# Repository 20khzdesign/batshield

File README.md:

Batshield
=========

An audio shield for arduino intended to develop audio synthesis and filtering.

Features
========

- MIDI input
- MIDI output
- Mic/Line input
- Line output
- 2 PWM output
- 4 switches
- 4 push buttons
- 5 knobs

The line output have been designed in order to be compatible with mozzi library
(http://sensorium.github.io/Mozzi/)

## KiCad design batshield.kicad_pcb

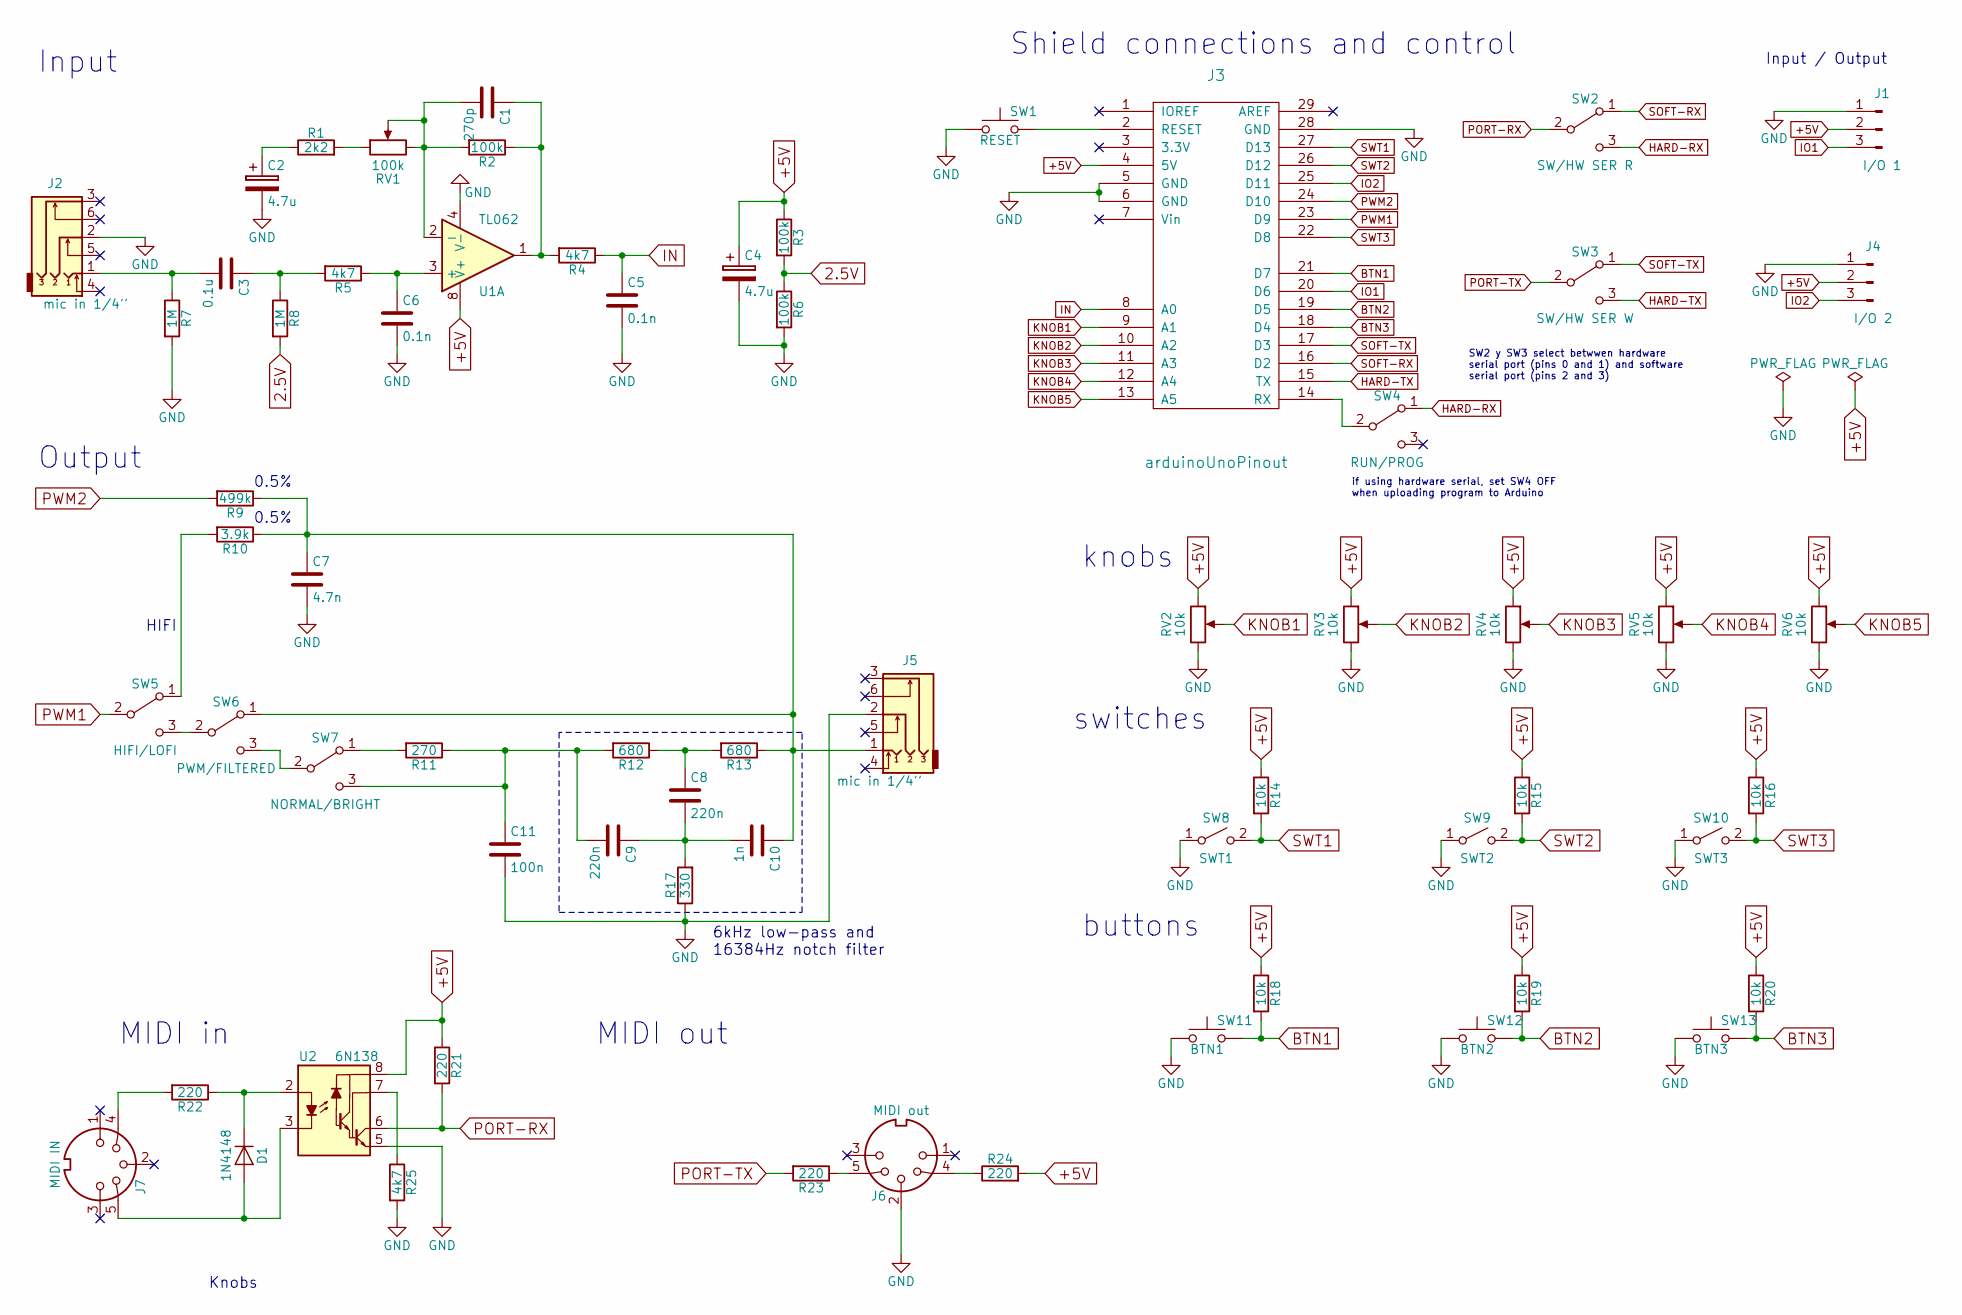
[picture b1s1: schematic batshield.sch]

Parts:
C1: 270p; C_Disc_D5.0mm_W2.5mm_P5.00mm
C2, C4: 4.7u; CP_Radial_D5.0mm_P2.50mm
C3: 0.1u; C_Disc_D5.0mm_W2.5mm_P5.00mm
C5, C6: 0.1n; C_Disc_D5.0mm_W2.5mm_P5.00mm
C7: 4.7n; C_Disc_D5.0mm_W2.5mm_P5.00mm
C8, C9: 220n; C_Disc_D5.0mm_W2.5mm_P5.00mm
C10: 1n; C_Disc_D5.0mm_W2.5mm_P5.00mm
C11: 100n; C_Disc_D5.0mm_W2.5mm_P5.00mm
D1: 1N4148; D_DO-35_SOD27_P7.62mm_Horizontal
J1: I/O 1; Pin_Header_Straight_1x03_Pitch2.54mm
J2, J5: mic in 1/4''; Jack_Female_6,35mm_HD
J3: arduinoUnoPinout
J4: I/O 2; Pin_Header_Straight_1x03_Pitch2.54mm
J6: MIDI out; MIDI_female_5_pins
J7: MIDI IN; MIDI_female_5_pins
R1: 2k2; R_Axial_DIN0207_L6.3mm_D2.5mm_P7.62mm_Horizontal
R2, R3, R6: 100k; R_Axial_DIN0207_L6.3mm_D2.5mm_P7.62mm_Horizontal
R4, R5, R25: 4k7; R_Axial_DIN0207_L6.3mm_D2.5mm_P7.62mm_Horizontal
R7, R8: 1M; R_Axial_DIN0207_L6.3mm_D2.5mm_P7.62mm_Horizontal
R9: 499k; R_Axial_DIN0207_L6.3mm_D2.5mm_P7.62mm_Horizontal
R10: 3.9k; R_Axial_DIN0207_L6.3mm_D2.5mm_P7.62mm_Horizontal
R11: 270; R_Axial_DIN0207_L6.3mm_D2.5mm_P7.62mm_Horizontal
R12, R13: 680; R_Axial_DIN0207_L6.3mm_D2.5mm_P7.62mm_Horizontal
R14, R15, R16, R18, R19, R20: 10k; R_Axial_DIN0207_L6.3mm_D2.5mm_P7.62mm_Horizontal
R17: 330; R_Axial_DIN0207_L6.3mm_D2.5mm_P7.62mm_Horizontal
R21, R22, R23, R24: 220; R_Axial_DIN0207_L6.3mm_D2.5mm_P7.62mm_Horizontal
RV1: 100k; potenciometro_PTV09
RV2, RV3, RV4, RV5, RV6: 10k; potenciometro_PTV09
SW1: RESET; SW_PUSH_6mm_h5mm
SW2: SW/HW SER R; interruptor_spdt
SW3: SW/HW SER W; interruptor_spdt
SW4: RUN/PROG; interruptor_spdt
SW5: HIFI/LOFI; interruptor_spdt
SW6: PWM/FILTERED; interruptor_spdt
SW7: NORMAL/BRIGHT; interruptor_spdt
SW8: SWT1; interruptor_spdt
SW9: SWT2; interruptor_spdt
SW10: SWT3; interruptor_spdt
SW11: BTN1; button_spst
SW12: BTN2; button_spst
SW13: BTN3; button_spst
U1: TL062; DIP-8_W7.62mm
U2: 6N138; DIP-8_W7.62mm

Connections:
2.5V: R3.2, R6.1, R8.2
+5V: C4.1, J1.2, J3.4 (5V), J4.2, R3.1, R14.1, R15.1, R16.1, R18.1, R19.1, R20.1, R21.1, R24.2, RV2.1, RV3.1, RV4.1, RV5.1, RV6.1, U1.8 (V+), U2.8
BTN1: J3.21 (D7), R18.2, SW11.2
BTN2: J3.19 (D5), R19.2, SW12.2
BTN3: J3.18 (D4), R20.2, SW13.2
GND: C2.2, C4.2, C5.2, C6.2, C7.2, C11.2, J1.1, J2.2, J3.5 (GND), J3.6 (GND), J3.28 (GND), J4.1, J5.2, J6.2, R6.2, R7.2, R17.1, R25.2, RV2.3, RV3.3, RV4.3, RV5.3, RV6.3, SW1.1, SW8.1 (A), SW9.1 (A), SW10.1 (A), SW11.1, SW12.1, SW13.1, U1.4 (V-), U2.5; also elsewhere on the board
HARD-RX: SW2.3 (C), SW4.1 (A)
HARD-TX: J3.15 (TX), SW3.3 (C)
IN: C5.1, J3.8 (A0), R4.1
IO1: J1.3, J3.20 (D6)
IO2: J3.25 (D11), J4.3
KNOB1: J3.9 (A1), RV2.2
KNOB2: J3.10 (A2), RV3.2
KNOB3: J3.11 (A3), RV4.2
KNOB4: J3.12 (A4), RV5.2
KNOB5: J3.13 (A5), RV6.2
unnamed: C1.1, R2.1, R4.2, U1.1
unnamed: C1.2, R2.2, RV1.2, RV1.3, U1.2 (-)
unnamed: C2.1, R1.1
unnamed: C3.1, R5.2, R8.1
unnamed 20: C3.2, J2.1, R7.1; also elsewhere on the board
unnamed: C6.1, R5.1, U1.3 (+)
unnamed: C8.1, R12.1, R13.2
unnamed 23: C7.1, C10.1, J5.1, R9.1, R10.1, R13.1, SW6.1 (A); also elsewhere on the board
unnamed: C8.2, C9.1, C10.2, R17.2
unnamed: C9.2, C11.1, R11.1, R12.2, SW7.3 (C)
unnamed: D1.1 (K), R22.1, U2.2
unnamed 27: D1.2 (A), J7.5, U2.3; also elsewhere on the board
unnamed: J3.2 (RESET), SW1.2
unnamed: J3.14 (RX), SW4.2 (B)
unnamed 44: J6.4, R24.1; also elsewhere on the board
unnamed 45: J6.5, R23.1; also elsewhere on the board
unnamed 49: J7.4, R22.2; also elsewhere on the board
unnamed: R1.2, RV1.1
unnamed: R10.2, SW5.1 (A)
unnamed: R11.2, SW7.1 (A)
unnamed: R25.1, U2.7
unnamed: SW5.3 (C), SW6.2 (B)
unnamed: SW6.3 (C), SW7.2 (B)
PORT-RX: R21.2, SW2.2 (B), U2.6
PORT-TX: R23.2, SW3.2 (B)
PWM1: J3.23 (D9), SW5.2 (B)
PWM2: J3.24 (D10), R9.2
SOFT-RX: J3.16 (D2), SW2.1 (A)
SOFT-TX: J3.17 (D3), SW3.1 (A)
SWT1: J3.27 (D13), R14.2, SW8.2 (B)
SWT2: J3.26 (D12), R15.2, SW9.2 (B)
SWT3: J3.22 (D8), R16.2, SW10.2 (B)

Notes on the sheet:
6kHz low-pass and 16384Hz notch filter
MIDI in
MIDI out
Knobs
HIFI
switches
Input / Output
Input
0.5%
Output
Shield connections and control
buttons
knobs
SW2 y SW3 select betwwen hardware serial port (pins 0 and 1) and software serial port (pins 2 and 3)
if using hardware serial, set SW4 OFF when uploading program to Arduino

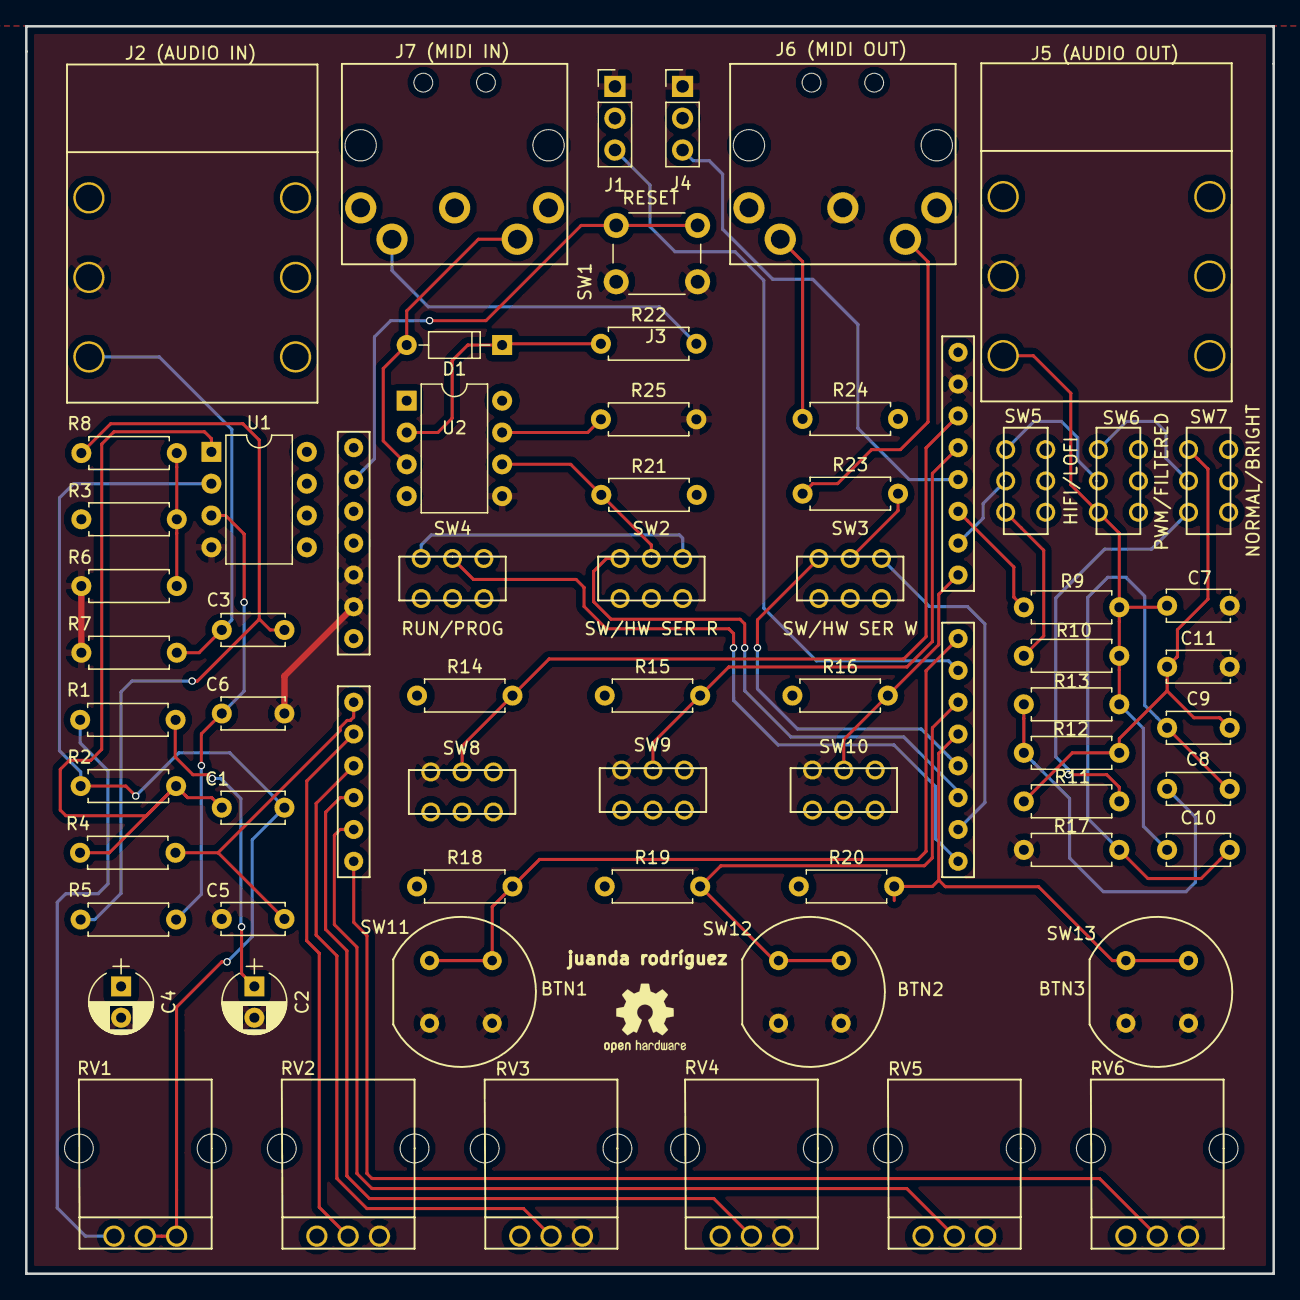
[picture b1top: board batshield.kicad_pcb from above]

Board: 2 copper layers, 99.6 x 99.6 mm, 65 parts (0 on the bottom side), 48 nets.

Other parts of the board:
J2 (AUDIO IN), J5 (AUDIO OUT): mic in 1/4''; Jack_Female_6,35mm_HD
J6 (MIDI OUT): MIDI out; MIDI_female_5_pins
J7 (MIDI IN): MIDI IN; MIDI_female_5_pins

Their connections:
GND: J2 (AUDIO IN).2, J5 (AUDIO OUT).2, J6 (MIDI OUT).2; also elsewhere on the board
unnamed 20: J2 (AUDIO IN).1; also elsewhere on the board
unnamed 23: J5 (AUDIO OUT).1; also elsewhere on the board
unnamed 27: J7 (MIDI IN).5; also elsewhere on the board
unnamed 44: J6 (MIDI OUT).4; also elsewhere on the board
unnamed 45: J6 (MIDI OUT).5; also elsewhere on the board
unnamed 49: J7 (MIDI IN).4; also elsewhere on the board

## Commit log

2017-10-09 commit inicial
2017-10-09 readme
2017-10-09 todos los elementos añadidos
2017-10-09 power folags
2017-10-10 corrección salida audio
2017-10-13 preamp para guitarra
2017-10-15 simulaciones spice y preamplificador per tutto
2017-10-15 simulaciones spice y preamplificador per tutto ii
2017-10-16 listo para prototipo con breadboard
2017-11-16 mejoras, mejoras, mejoras
2017-11-21 pcb pasando drc
2017-11-25 añado algunos modelos 3d
2017-11-25 quito transistor del circuito midi out
2017-12-17 reduciendo el tamaño de la placa unos milimetros cuadrados
2017-12-17 reduciendo el tamaño de la placa unos milimetros cuadrados ...
2017-12-18 reducido a un tamaño aprox de 100mm x 100mm
2017-12-19 reducidooooo
2018-11-17 añado Bill Of Materials
2018-11-17 cambio bom a doc

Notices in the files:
batshield.kicad_pcb:
Creative Common. Attribution-ShareAlike 4.0 International (CC BY-SA 4.0)
batshield.sch:
https://creativecommons.org/licenses/by-sa/4.0
